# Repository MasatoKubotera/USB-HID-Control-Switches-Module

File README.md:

<html lang="en">

<head>
	<meta charset="uft-8">
	<meta name="author" content="Masato Kubotera">
    <meta name="description" content="">
</head>

<body>
    <p><strong>This product is currently under development!</strong></p>
	<h1>USB-HID Control Switches Module</h1>
        <p>
            This product is a USB-HID module equipped with two tactile switches. The module is recognized as a game controller when connected to a computer with an Arduino compatible board equipped with ATmega32U4. Using the sample firmware, a press of the two tactile switches on the board is recognized as a press of game controller buttons 1 and 2, respectively.<br>
            This product is developed as a control switches for <a href="https://github.com/SUSTAINA-OP">SUSTAINA-OP<sup>TM</sup></a>, it is used to start or stop the robot's behavior.
        </p>
	<h2>Features Rev. 1</h2>
        <p>
            <table>
                <tr>
                    <th>Top Surface of PCB</th>
                    <th>Bottom Surface of PCB</th>
                    <th>Assembled Electronic Components</th>
                </tr>
                <tr>
                    <td></td>
                    <td></td>
                    <td></td>
                </tr>
            </table>
        </p>
    <h3>PCB</h3>
        <p>
            <ul>
                <li>58 mm x 22.5 mm PCB layout</li>
                <li>2 x ø3.2 Mounting Holes</li>
            </ul>
        </p>
    <h3>Dual Tactile Switches</h3>
        <p>
            NKK Switches JF Series (Green: JF15SP1F, Red: JF15SP1C)
            <ul>
                <li>Contact Rating: 0.05A @ 24VDC</li>
                <li>Circuits: Off-Mom</li>
                <li>Outline: 17.70mm x 17.70mm</li>
                <li>Operating Force: 300gf</li>
            </ul>
        </p>
	<h2>Development Environments</h2>
    <p>
        This product is designed with the following software.
            <ul>
                <li><a href="https://www.autodesk.com/products/eagle/overview">Autodesk Eagle 9.6.2</a></li>
            </ul>
    </p>
    <h2>Repository Contents</h2>
        <p>
            <dl>
                <dt><a href="/images">\images</a></dt>
                <dd>PCB preview images and capture of design screen</dd>
                <dt><a href="/libraries">\libraries</a></dt>
                <dd>Libraries used in Autodesk Eagle design</dd>
                <dt><a href="/documents">\documents</a> </dt>
                <dd>Documentation for making and using this product</dd>
                <dt><a href="/pcb_order">\pcb_order</a> </dt>
                <dd>Gerber data and documentation for ordering PCB</dd>
                <dt><a href="/firmware">\firmware</a> </dt>
                <dd>Sample firmware to be written to the microcontroller board</dd>
                <dt><a href="/schematic.pdf">schematic.pdf</a></dt>
                <dd>Circuit diagram of this product</dd>
                <dt>*.brd</dt>
                <dd>Board wiring design file by Autodesk Eagle</dd>
                <dt>*.sch</dt>
                <dd>Circuit diagram design file by Autodesk Eagle</dd>
                <dt><a href="/.gitignore">.gitignore</a></dt>
                <dd>A file that tells Git not to track a particular file</dd>
                <dt><a href="/LICENSE">LICENSE</a></dt>
                <dd>License to use this product</dd>
            </dl>
        </p>
    <h2>Documentation</h2>
        <p>
            The following documents are available for this product.
            <ul>
                <li><a href="/documents/BOM.md">\document\BOM.md</a>: List of electronic components assembled on the PCB</li>
            </ul>
        </p>
    <h2>References</h2>
        <p>
            This product was designed with reference to the following products.
            <ul>
                <li></li>
            </ul>
        </p>
    <h2>Contact</h2>
        <p>
            If you have any questions, please contact the designer of this product, Masato Kubodera, by <a href="mailto:masato.kubotera@sustaina-op.com">e-mail</a>.<br>
            E-mail: <a href="mailto:masato.kubotera@sustaina-op.com">masato.kubotera@sustaina-op.com</a>
        </p>
    <h2>License Information</h2>
        <p>
            This product is open source. Please review the <a href="/LICENSE">LICENSE</a> for license information.<br>
            <br>
            This product by Masato Kubotera is licensed under a <a href="http://creativecommons.org/licenses/by-nc-sa/4.0/">Creative Commons Attribution-NonCommercial-ShareAlike 4.0 International License</a>.
        </p>
</body>
</html>

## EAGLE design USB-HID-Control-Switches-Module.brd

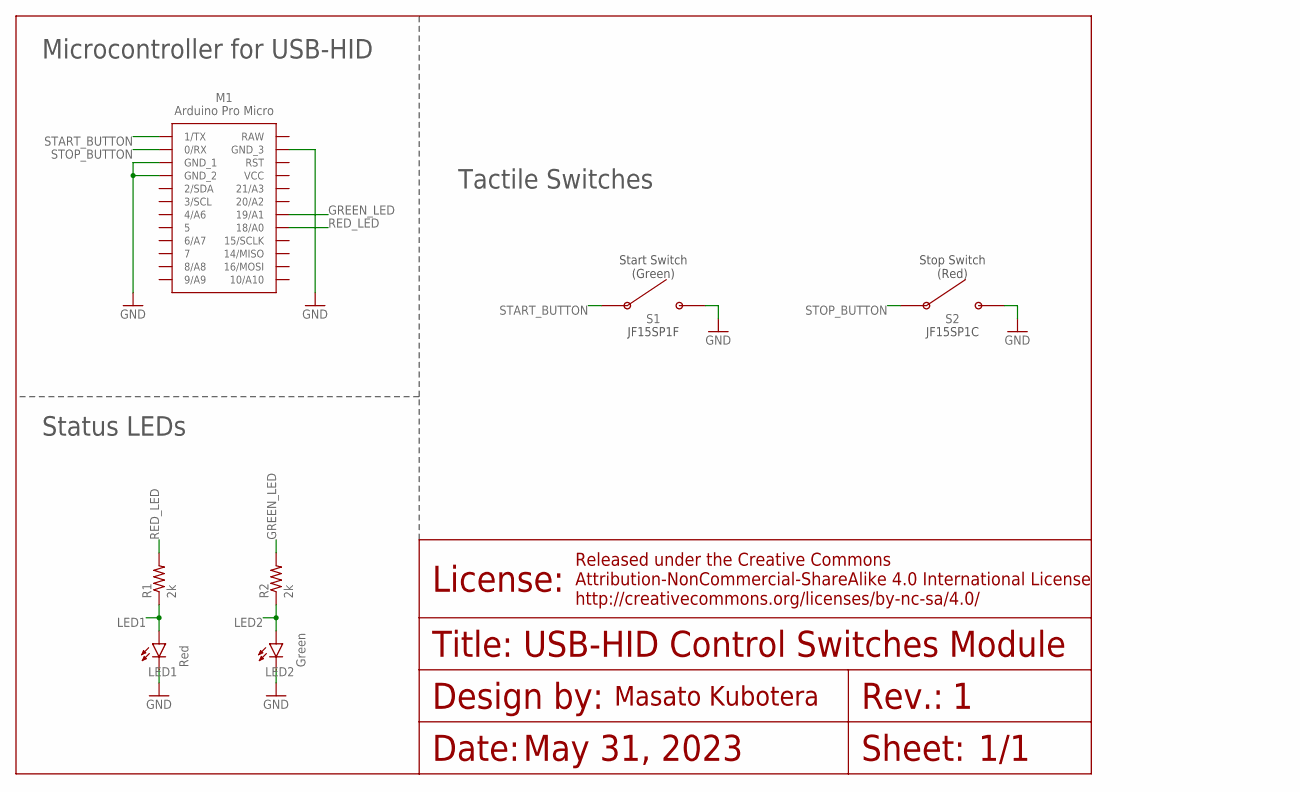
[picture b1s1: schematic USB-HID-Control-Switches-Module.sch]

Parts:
LED1: Red; SML0603
LED2: Green; SML0603
M1: PRO_MICRO_SMD
R1, R2: 2k; R0603
S1: JF15SP1F; JF15SP1
S2: JF15SP1C; JF15SP1

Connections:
GND: LED1.C, LED2.C, M1.3 (GND_1), M1.4 (GND_2), M1.23 (GND_3), S1.3, S1.4, S2.3, S2.4
GREEN_LED: M1.18 (19/A1), R2.2
LED1: LED1.A, R1.1
LED2: LED2.A, R2.1
RED_LED: M1.17 (18/A0), R1.2
START_BUTTON: M1.1 (1/TX), S1.1, S1.2
STOP_BUTTON: M1.2 (0/RX), S2.1, S2.2

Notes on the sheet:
Start Switch (Green)
Stop Switch (Red)
Microcontroller for USB-HID
Tactile Switches
1/1
May 31, 2023
USB-HID Control Switches Module
Status LEDs

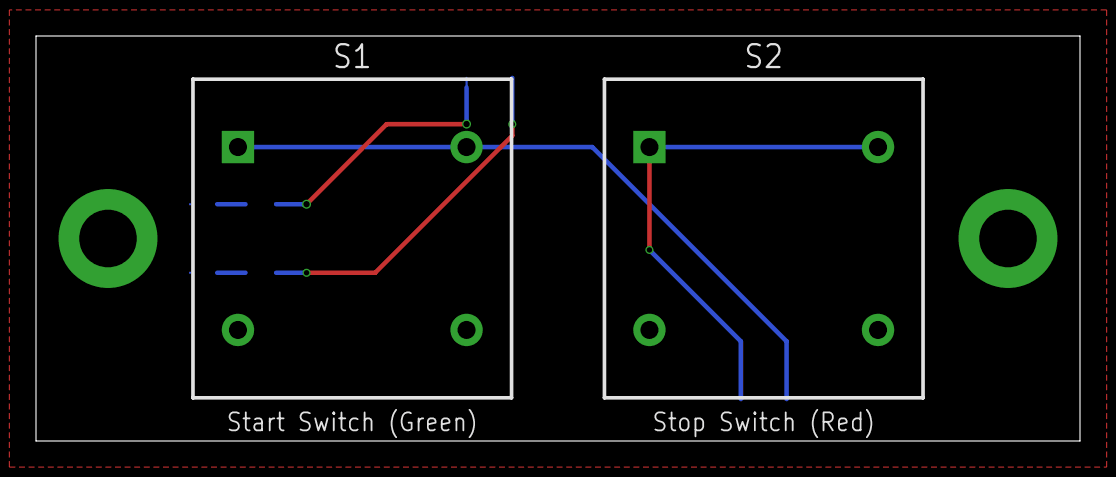
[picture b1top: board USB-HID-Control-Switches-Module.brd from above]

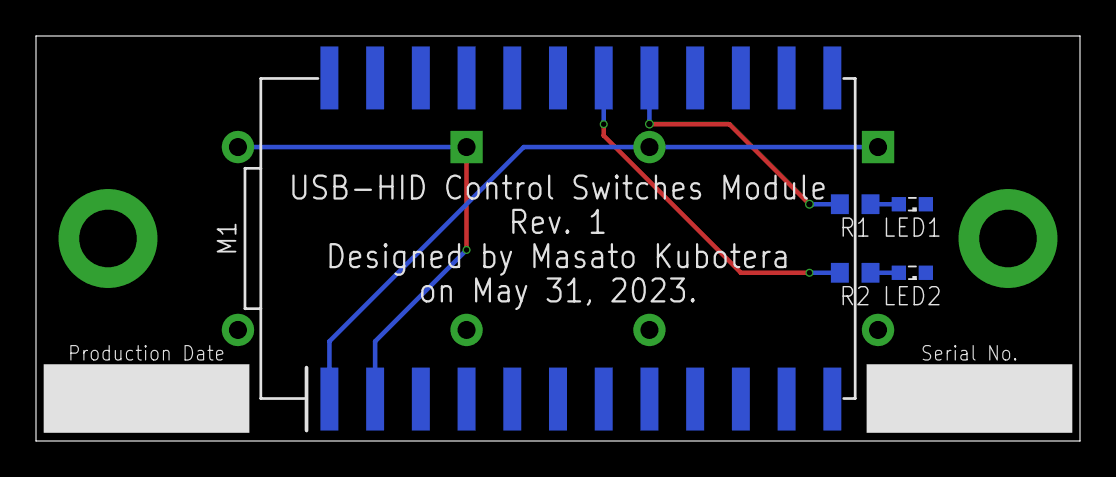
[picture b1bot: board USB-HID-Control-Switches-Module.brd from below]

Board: 2 copper layers, 58.0 x 22.5 mm, 7 parts (5 on the bottom side), 7 nets.

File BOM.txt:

Qty Value         Device        Package       Parts Description 
1   JF15SP1C      JF15SP1C      JF15SP1       S2                
1   JF15SP1F      JF15SP1F      JF15SP1       S1                
1   PRO_MICRO_SMD PRO_MICRO_SMD PRO_MICRO_SMD M1

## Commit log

2023-05-19 Initial upload
2023-05-19 Fixed firmware hierarchy
2023-05-20 Change the mounting orientation of the microcontroller board
2023-05-20 Added documentation and data on PCB order
2023-05-31 Additional LED for status check
2023-06-02 Add files for PCBA (not used)
2023-06-14 Update README.md for additional LED for status check
2023-06-14 Changed the color of the board preview to a shade closer to the actual color
2023-06-29 Changed to firmware using status indicator LEDs

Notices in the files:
parts and their libraries:
Frames: Released under the Creative Commons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
